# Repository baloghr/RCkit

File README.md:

# RCkit
Simple RC kit for teaching basics of control system

It is a simple extension board (shield) for Arduino Nano, but connectible also to any other Arduinos. Board contains few RC circuits creating a system of modules representing the 1st and/or 2nd order systems in various configurations. User can control the system from the Arduino using e.g. PID control algorithms and measure the system responses. Combination with Matlab/Simulink is also possible. 

Initial design was done by students András Blahó and Filip Brhlík during their diploma projects. 

More information can be found in the following paper:

Žáková, Katarína and Richard Balogh. "Control Engineering Home Learning Kit." IFAC-PapersOnLine, vol. 55, no. 4, 1 Jan. 2022, pp. 310-5, doi:10.1016/j.ifacol.2022.06.051.

The paper is available at the https://www.sciencedirect.com/science/article/pii/S2405896322003664

See also a

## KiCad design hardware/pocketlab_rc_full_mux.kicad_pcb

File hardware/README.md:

Here are the design files for KiCAD 5.0

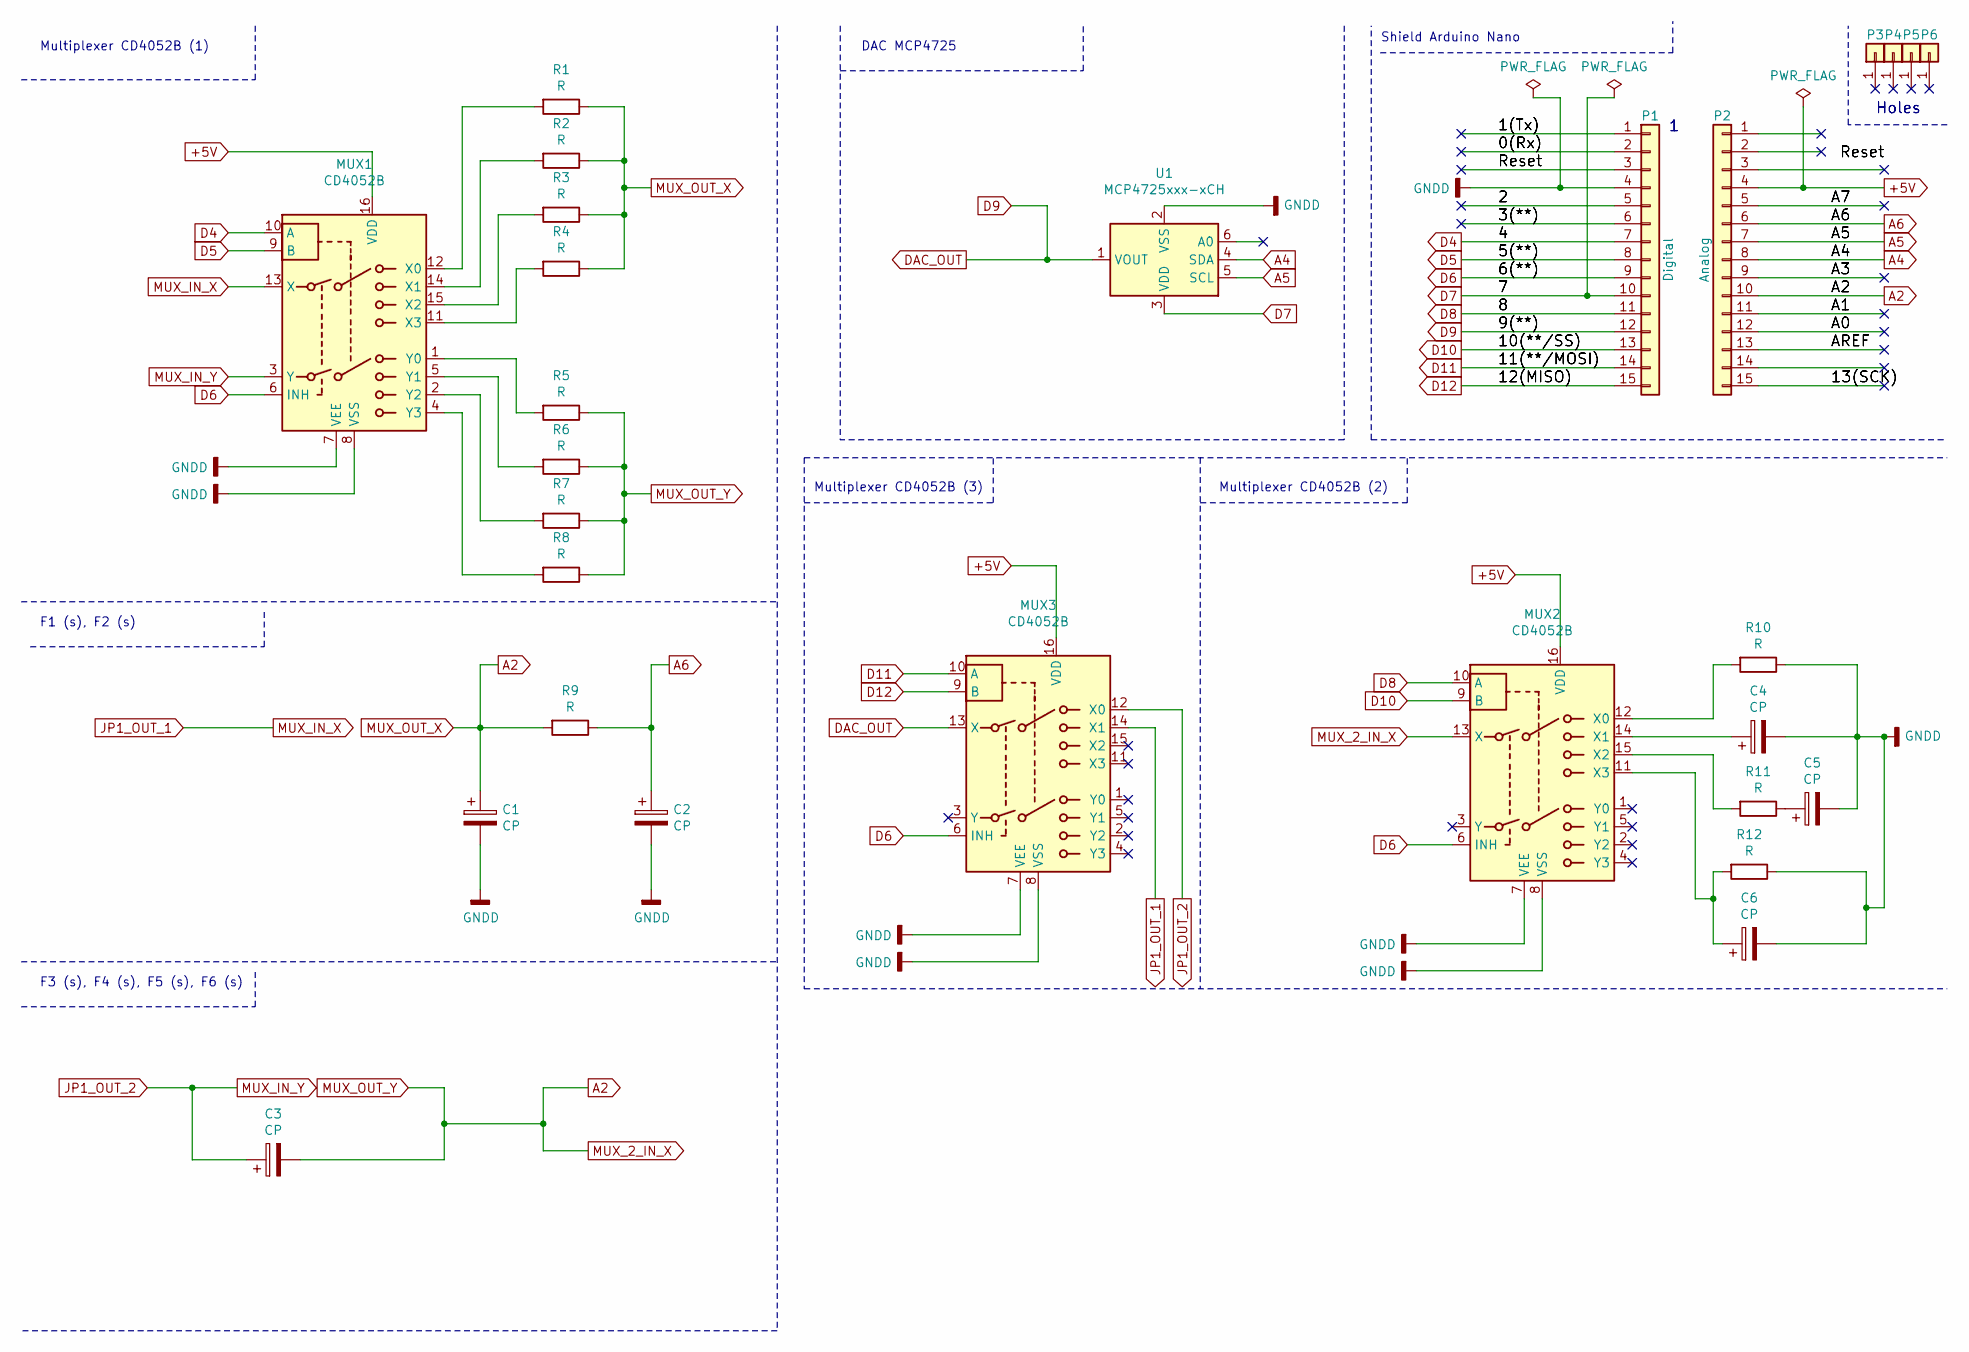
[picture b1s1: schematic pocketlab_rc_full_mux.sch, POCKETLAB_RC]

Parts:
C1, C2, C3, C4, C5, C6: CP; C_0805_2012Metric_Pad1.18x1.45mm_HandSolder
MUX1, MUX2, MUX3: CD4052B; SOP65P640X120-16N
P1: Digital; Socket_Strip_Arduino_1x15
P2: Analog; Socket_Strip_Arduino_1x15
P3, P4, P5, P6: CONN_01X01; 1pin_Nano
R1, R2, R3, R4, R5, R6, R7, R8, R9, R10, R11, R12: R; R_0805_2012Metric_Pad1.20x1.40mm_HandSolder
U1: MCP4725xxx-xCH; SOT95P270X145-6N

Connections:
+5V: MUX1.16 (VDD), MUX2.16 (VDD), MUX3.16 (VDD), P2.4
/0(Rx): P1.2
/1(Tx): P1.1
/2: P1.5
/3(**): P1.6
/13(SCK): P2.15
/A0: P2.12
/A1: P2.11
/A3: P2.9
/A7: P2.5
/AREF: P2.13
/Reset: P1.3
A2: C1.1, C3.2, MUX2.13 (X), P2.10, R1.1, R2.1, R3.1, R4.1, R5.1, R6.1, R7.1, R8.1, R9.2
A4: P2.8, U1.4 (SDA)
A5: P2.7, U1.5 (SCL)
A6: C2.1, P2.6, R9.1
D4: MUX1.10 (A), P1.7
D5: MUX1.9 (B), P1.8
D6: MUX1.6 (INH), MUX2.6 (INH), MUX3.6 (INH), P1.9
D7: P1.10, U1.3 (VDD)
D8: MUX2.10 (A), P1.11
D9: MUX3.13 (X), P1.12, U1.1 (VOUT)
D10: MUX2.9 (B), P1.13
D11: MUX3.10 (A), P1.14
D12: MUX3.9 (B), P1.15
GNDD: C1.2, C2.2, C4.2, C5.2, C6.2, MUX1.7 (VEE), MUX1.8 (VSS), MUX2.7 (VEE), MUX2.8 (VSS), MUX3.7 (VEE), MUX3.8 (VSS), P1.4, R10.1, R12.1, U1.2 (VSS)
JP1_OUT_1: MUX1.13 (X), MUX3.14 (X1)
JP1_OUT_2: C3.1, MUX1.3 (Y), MUX3.12 (X0)
unnamed: C4.1, MUX2.14 (X1)
unnamed: C5.1, R11.1
unnamed: C6.1, MUX2.11 (X3), R12.2
unnamed: MUX1.1 (Y0), R5.2
unnamed: MUX1.2 (Y2), R7.2
unnamed: MUX1.4 (Y3), R8.2
unnamed: MUX1.5 (Y1), R6.2
unnamed: MUX1.11 (X3), R4.2
unnamed: MUX1.12 (X0), R1.2
unnamed: MUX1.14 (X1), R2.2
unnamed: MUX1.15 (X2), R3.2
unnamed: MUX2.12 (X0), R10.2
unnamed: MUX2.15 (X2), R11.2

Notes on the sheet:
Holes
DAC MCP4725
Multiplexer CD4052B (1)
F1 (s), F2 (s)
Shield Arduino Nano
F3 (s), F4 (s), F5 (s), F6 (s)
Multiplexer CD4052B (2)
Multiplexer CD4052B (3)

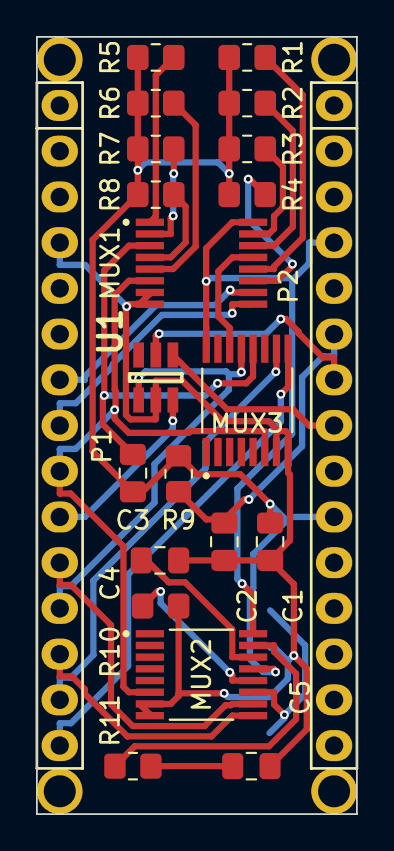
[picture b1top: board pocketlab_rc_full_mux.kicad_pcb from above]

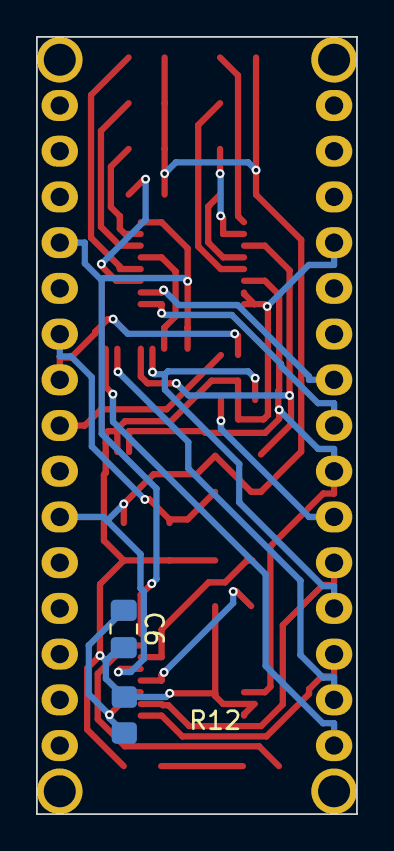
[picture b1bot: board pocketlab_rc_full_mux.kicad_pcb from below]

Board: 2 copper layers, 17.8 x 43.2 mm, 28 parts (2 on the bottom side), 30 nets.

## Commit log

2023-12-20 Configuration diagram to help with programming
2023-12-20 Update README.md
    Updated configuration info
